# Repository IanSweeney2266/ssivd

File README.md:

# Small Scale Intelligent Vehicle Design platform (SSIVD)
Software and hardware documentation for creating an implementation of the Cal Poly SLO small-scale intelligent vehicle design platform

All original work is licensed under the MIT license, and all derivative work is licensed under the appropriate parent license 

If there are any concerns regarding licensing, get in touch and we will attempt to resolve it as soon as possible

#Statement of Disclaimer

Since this project is a result of a class assignment, it has been graded and accepted as fulfillment of the
course requirements. Acceptance does not imply technical accuracy or reliability. Any use of information
in this report is done at the risk of the user. These risks may include catastrophic failure of the device or
infringement of patent or copyright laws. California Polytechnic State University at San Luis Obispo and
its staff cannot be held liable for any use or misuse of the project.

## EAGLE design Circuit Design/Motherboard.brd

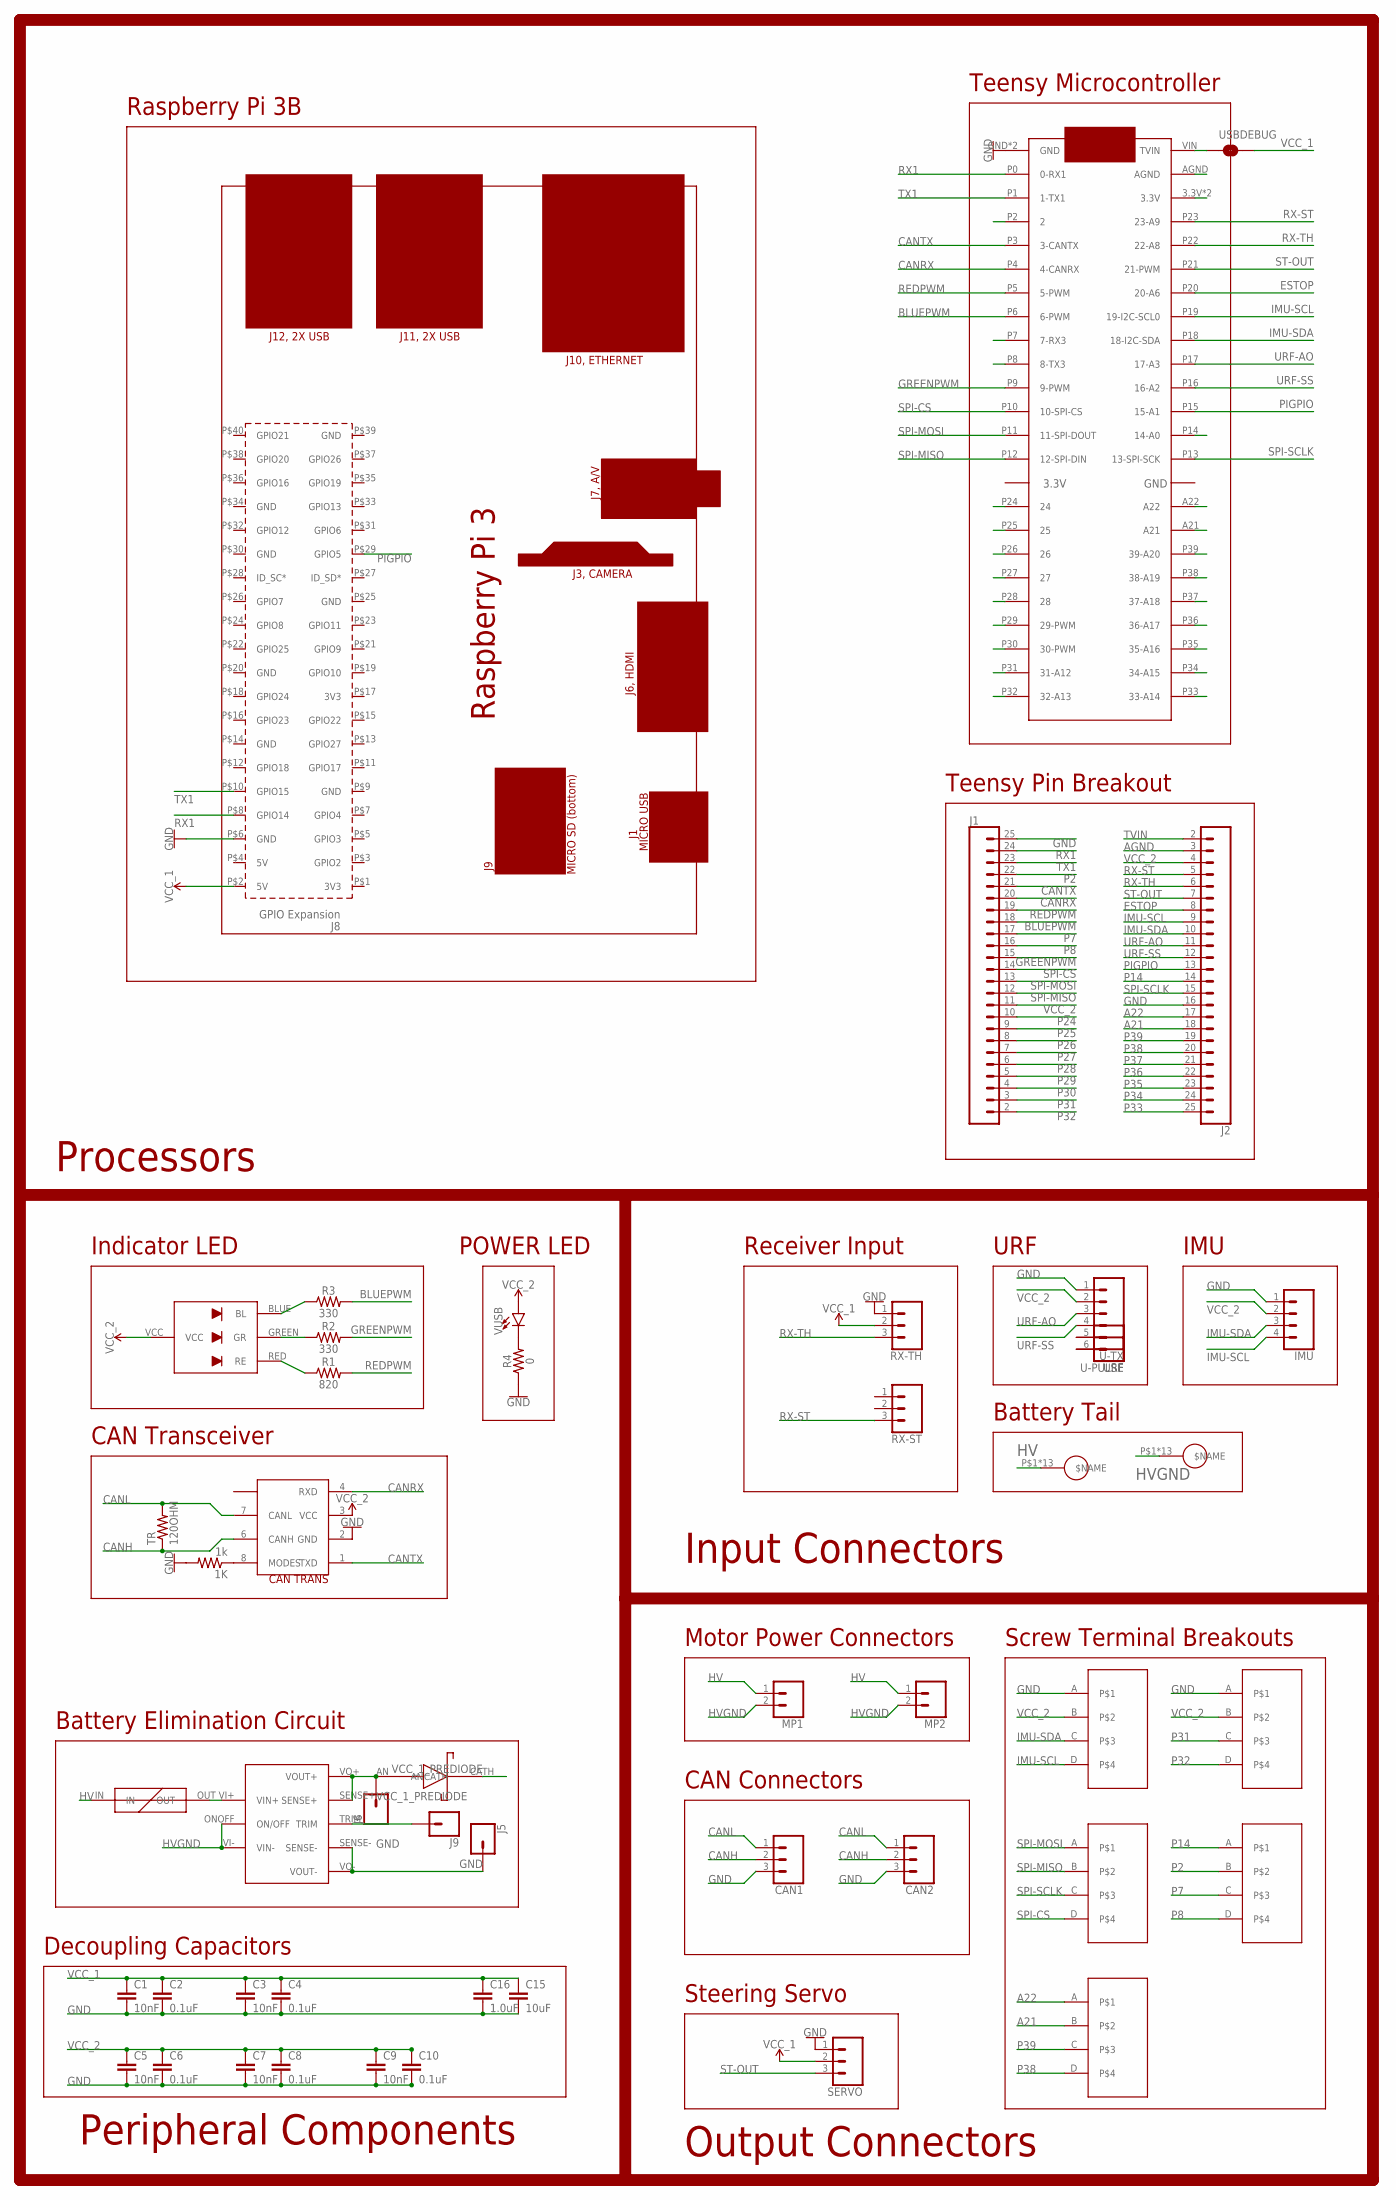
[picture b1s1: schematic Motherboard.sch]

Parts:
1K: 1k; R0603
C1, C3, C5, C7, C9: 10nF; 0603
C2, C4, C6, C8, C10: 0.1uF; 0603
C15: 10uF; 1206
C16: 1.0uF; 1206
CAN1, CAN2: CONN_03SCREW; SCREWTERMINAL-3.5MM-3
DAC/ADC: SCREWTERM
HV+: WIREPAD
HV-: WIREPAD
I2C: SCREWTERM
IMU: CONN_041X04_NO_SILK; 1X04_NO_SILK
J1, J2: CONN_24; 1X24
J5, J6, J9: CONN_01PTH_NO_SILK_YES_STOP; 1X01_NO_SILK
MP1, MP2: CONN_023.5MM; SCREWTERMINAL-3.5MM-2
PCB1: RPI3
PWM: SCREWTERM
R1: 820; 0603
R2, R3: 330; 0603
R4: 0; 0603
RPI-SPI: SCREWTERM
RX-ST: CONN_03; 1X03
RX-TH: CONN_03; 1X03
SERVO: CONN_03; 1X03
TEENS: TEENSY3.6
TR: 120OHM; R0603
U$1: CREERGB
U$2: CAN-TRANS; SO08
U$4: BEC
U$5: LITTLEFUSE
U$6: SCHOTTKY; 2114
U-PULSE: CONN_01PTH_NO_SILK_YES_STOP; 1X01_NO_SILK
U-TX: CONN_01PTH_NO_SILK_YES_STOP; 1X01_NO_SILK
UART: SCREWTERM
URF: CONN_06NO_SILK_FEMALE_PTH; 1X06_NO_SILK
USBDEBUG: JUMPER-SMT_2_NO_NO-SILK; SMT-JUMPER_2_NO_NO-SILK
VUSB: LED0603; LED-0603

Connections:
A21: DAC/ADC.B, J2.18, TEENS.A21
A22: DAC/ADC.A, J2.17, TEENS.A22
AGND: J2.3, TEENS.AGND
BLUEPWM: J1.18, R3.2, TEENS.P6 (6-PWM)
CANH: CAN1.2, CAN2.2, TR.1, U$2.6 (CANH)
CANL: CAN1.1, CAN2.1, TR.2, U$2.7 (CANL)
CANRX: J1.20, TEENS.P4 (4-CANRX), U$2.4 (RXD)
CANTX: J1.21, TEENS.P3 (3-CANTX), U$2.1 (TXD)
ESTOP: J2.8, TEENS.P20 (20-A6)
FUSEDHV: U$4.VI+ (VIN+), U$5.OUT
GND: 1K.2, C1.2, C2.2, C3.2, C4.2, C5.2, C6.2, C7.2, C8.2, C9.2, C10.2, C15.2, C16.2, CAN1.3, CAN2.3, I2C.A, IMU.1, J1.25, J2.16, J5.1, PCB1.P$6 (GND), R4.1, RX-TH.1, SERVO.1, TEENS.GND, TEENS.GND2 (GND), U$2.2 (GND), U$4.SENSE-, U$4.VO- (VOUT-), UART.A, URF.1
GREENPWM: J1.15, R2.2, TEENS.P9 (9-PWM)
HV: HV+.P$1, HV+.P$2, HV+.P$3, HV+.P$4, HV+.P$5, HV+.P$6, HV+.P$7, HV+.P$8, HV+.P$9, HV+.P$10, HV+.P$11, HV+.P$12, HV+.P$13, MP1.1, MP2.1, U$5.IN
HVGND: HV-.P$1, HV-.P$2, HV-.P$3, HV-.P$4, HV-.P$5, HV-.P$6, HV-.P$7, HV-.P$8, HV-.P$9, HV-.P$10, HV-.P$11, HV-.P$12, HV-.P$13, MP1.2, MP2.2, U$4.ONOFF (ON/OFF), U$4.VI- (VIN-)
IMU-SCL: I2C.D, IMU.4, J2.9, TEENS.P19 (19-I2C-SCL0)
IMU-SDA: I2C.C, IMU.3, J2.10, TEENS.P18 (18-I2C-SDA)
unnamed: U-PULSE.1, URF.6
unnamed: U-TX.1, URF.5
unnamed: 1K.1, U$2.8 (MODES)
unnamed: R4.2, VUSB.C
unnamed: J9.1, U$4.TRIM
unnamed: R1.1, U$1.RED (RE)
unnamed: R2.1, U$1.GREEN (GR)
unnamed: R3.1, U$1.BLUE (BL)
P2: J1.22, PWM.B, TEENS.P2 (2)
P7: J1.17, PWM.C, TEENS.P7 (7-RX3)
P8: J1.16, PWM.D, TEENS.P8 (8-TX3)
P14: J2.14, PWM.A, TEENS.P14 (14-A0)
P24: J1.10, TEENS.P24 (24)
P25: J1.9, TEENS.P25 (25)
P26: J1.8, TEENS.P26 (26)
P27: J1.7, TEENS.P27 (27)
P28: J1.6, TEENS.P28 (28)
P29: J1.5, TEENS.P29 (29-PWM)
P30: J1.4, TEENS.P30 (30-PWM)
P31: J1.3, TEENS.P31 (31-A12), UART.C
P32: J1.2, TEENS.P32 (32-A13), UART.D
P33: J2.25, TEENS.P33 (33-A14)
P34: J2.24, TEENS.P34 (34-A15)
P35: J2.23, TEENS.P35 (35-A16)
P36: J2.22, TEENS.P36 (36-A17)
P37: J2.21, TEENS.P37 (37-A18)
P38: DAC/ADC.D, J2.20, TEENS.P38 (38-A19)
P39: DAC/ADC.C, J2.19, TEENS.P39 (39-A20)
PIGPIO: J2.13, PCB1.P$29 (GPIO5), TEENS.P15 (15-A1)
REDPWM: J1.19, R1.2, TEENS.P5 (5-PWM)
RX1: J1.24, PCB1.P$8 (GPIO14), TEENS.P0 (0-RX1)
RX-ST: J2.5, RX-ST.3, TEENS.P23 (23-A9)
RX-TH: J2.6, RX-TH.3, TEENS.P22 (22-A8)
SPI-CS: J1.14, RPI-SPI.D, TEENS.P10 (10-SPI-CS)
SPI-MISO: J1.12, RPI-SPI.B, TEENS.P12 (12-SPI-DIN)
SPI-MOSI: J1.13, RPI-SPI.A, TEENS.P11 (11-SPI-DOUT)
SPI-SCLK: J2.15, RPI-SPI.C, TEENS.P13 (13-SPI-SCK)
ST-OUT: J2.7, SERVO.3, TEENS.P21 (21-PWM)
TVIN: J2.2, TEENS.VIN (TVIN), USBDEBUG.1
TX1: J1.23, PCB1.P$10 (GPIO15), TEENS.P1 (1-TX1)
URF-AO: J2.11, TEENS.P17 (17-A3), URF.3
URF-SS: J2.12, TEENS.P16 (16-A2), URF.4
VCC_1: C1.1, C2.1, C3.1, C4.1, C15.1, C16.1, PCB1.P$2 (5V), RX-TH.2, SERVO.2, U$6.CATH, USBDEBUG.2
VCC_1_PREDIODE: J6.1, U$4.SENSE+, U$4.VO+ (VOUT+), U$6.AN
VCC_2: C5.1, C6.1, C7.1, C8.1, C9.1, C10.1, I2C.B, IMU.2, J1.11, J2.4, TEENS.3.3V, TEENS.3.3V2 (3.3V), U$1.VCC, U$2.3 (VCC), UART.B, URF.2, VUSB.A

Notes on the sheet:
Processors
Input Connectors
Output Connectors
Peripheral Components
Teensy Pin Breakout
Teensy Microcontroller
Raspberry Pi 3B
CAN Transceiver
Indicator LED
Motor Power Connectors
CAN Connectors
Steering Servo
Receiver Input
URF
IMU
Battery Tail
Battery Elimination Circuit
Screw Terminal Breakouts
Decoupling Capacitors
POWER LED

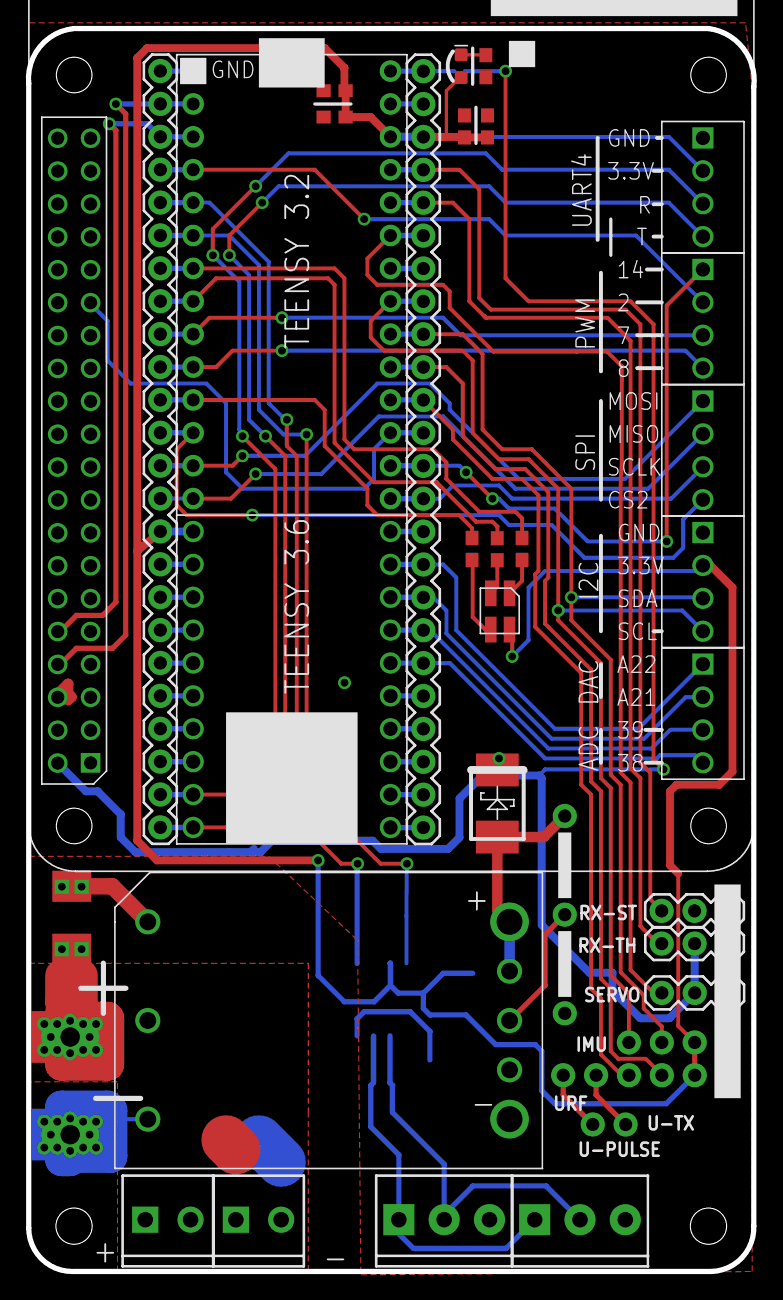
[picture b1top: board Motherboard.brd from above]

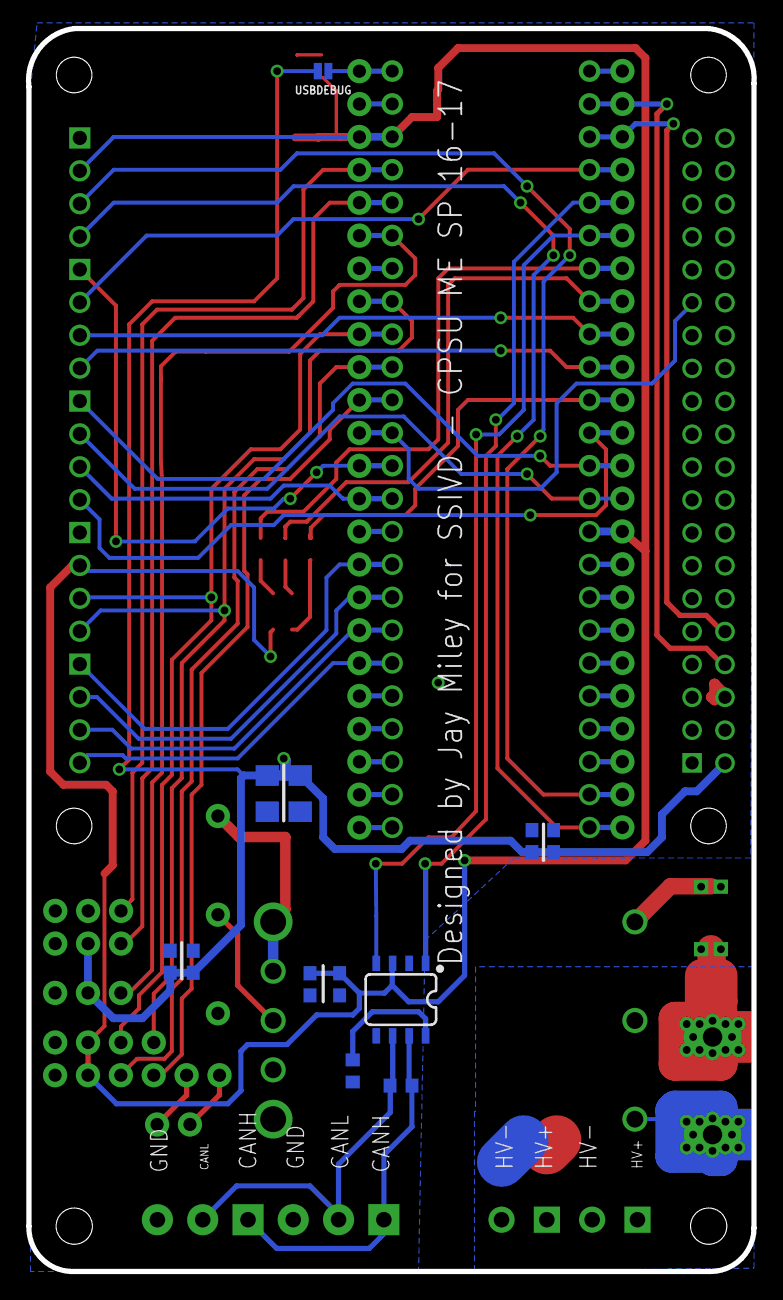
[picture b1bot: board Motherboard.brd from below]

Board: 2 copper layers, 56.0 x 96.0 mm, 50 parts (13 on the bottom side), 61 nets.

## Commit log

2017-05-23 Added timeline
2017-06-13 Added MIT License
2017-06-13 Create license
2017-06-13 Created Mech Folder
2017-06-13 Added motherboard files
2017-06-13 Added design reports
2017-06-14 Added measured stock parts
2017-06-14 Custom 3d parts
2017-06-14 Added rest of parts
2017-06-15 Automation Files
2017-06-16 Updated readme to reflect fully populated state

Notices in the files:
parts and their libraries:
SparkFun-Connectors: Licensing: Creative Commons ShareAlike 4.0 International - https://creativecommons.org/licenses/by-sa/4.0
